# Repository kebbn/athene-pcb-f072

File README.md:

# athene-pcb-f072
 65% PCB design for the Athene keyboard by KL using the STM32F072 MCU.

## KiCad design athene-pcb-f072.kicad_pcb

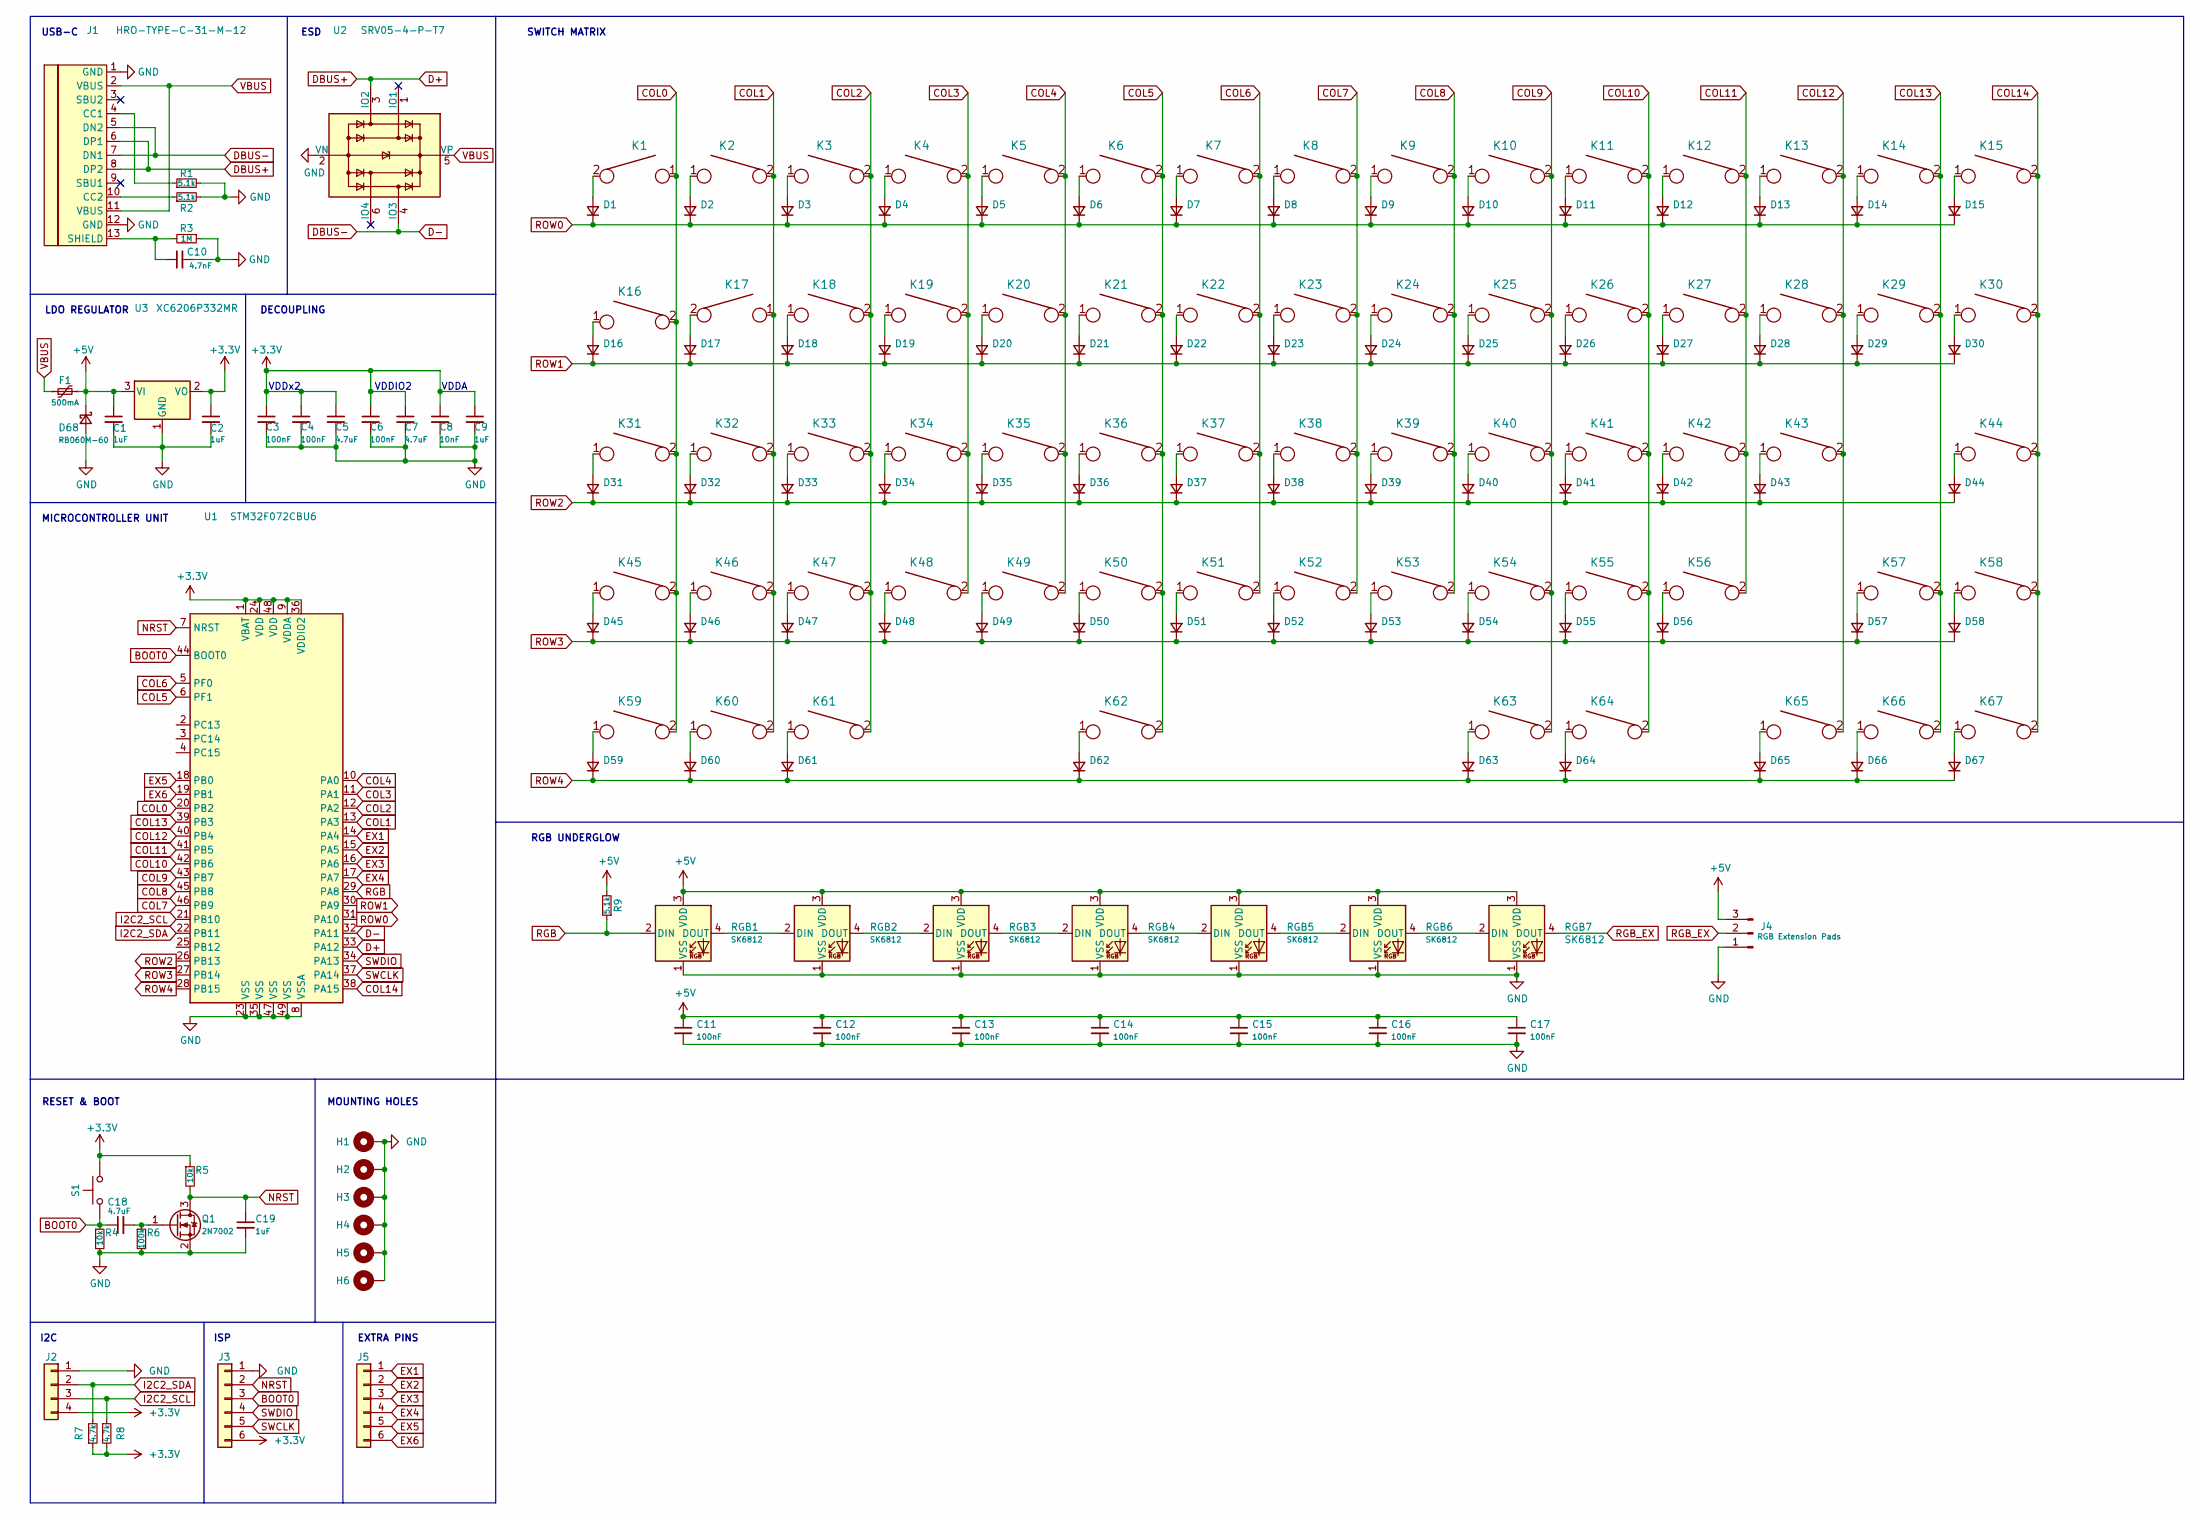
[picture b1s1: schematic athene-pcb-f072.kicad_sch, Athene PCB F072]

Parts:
C1, C2, C9: 1uF; C_0805_2012Metric; LCSC C28323
C3, C4, C6, C11, C12, C13, C14, C15, C16, C17: 100nF; C_0805_2012Metric; LCSC C49678
C5, C7: 4.7uF; C_0805_2012Metric; LCSC C1779
C8: 10nF; C_0805_2012Metric; LCSC C1710
C10: 4.7nF; C_0805_2012Metric; LCSC C1744
C18: 4.7uF; C_0805_2012Metric; LCSC C1744
C19: 1uF; C_0805_2012Metric; LCSC C15850
D1, D2, D3, D4, D5, D6, D7, D8, D9, D10, D11, D12, D13, D14, D15, D16, D17, D18, D19, D20, D21, D22, D23, D24, D25, D26, D27, D28, D29, D30, D31, D32, D33, D34, D35, D36, D37, D38, D39, D40, D41, D42, D43, D44, D45, D46, D47, D48, D49, D50, D51, D52, D53, D54, D55, D56, D57, D58, D59, D60, D61, D62, D63, D64, D65, D66, D67: 1N4148W; D_SOD-123; LCSC C81598
D68: RB060M-60; D_SOD-123; LCSC C115330
F1: 500mA; Fuse_1206_3216Metric; LCSC C151162
H1, H2, H4, H6: Poker_oval_hole
H3, H5: MountingHole_M2
J1: HRO-TYPE-C-31-M-12
J2: I2C; SolderWirePad_1x04_P3.175mm_Drill0.8mm
J3: ISP; ICSP-Header
J4: RGB Extension Pads; SolderWirePad_1x03_P3.175mm_Drill0.8mm
J5: EX; 6-Pin Header
K1, K2, K3, K4, K5, K6, K7, K8, K9, K10, K11, K12, K13, K14, K15, K16, K17, K18, K19, K20, K21, K22, K23, K24, K25, K26, K27, K28, K30, K31, K32, K33, K34, K35, K36, K38, K39, K40, K41, K42, K43, K44, K45, K46, K47, K48, K49, K50, K51, K52, K53, K54, K55, K56, K57, K58, K59, K61, K62, K63, K64, K65, K67: KEYSW; Kailh_MX_Socket (3D)
K29, K37, K60, K66: KEYSW; Kailh_MX_Socket (3D) 1_Circle
Q1: 2N7002; SOT-23; LCSC C8545
R1, R2, R9: 5.1k; R_0805_2012Metric; LCSC C27834
R3: 1M; R_0805_2012Metric; LCSC C17514
R4, R5: 10k; R_0805_2012Metric; LCSC C17414
R6: 100k; R_0805_2012Metric; LCSC C17407
R7, R8: 4.7k; R_0805_2012Metric; LCSC C17673
RGB1, RGB2, RGB3, RGB4, RGB5, RGB6, RGB7: SK6812; SK6812_Mini
S1: TS-1187A-B-A-B; SKQG-1155865; LCSC C318884
U1: STM32F072CBU6; QFN-48-1EP_7x7mm_P0.5mm_EP5.6x5.6mm; LCSC C92504
U2: SRV05-4-P-T7; SOT-23-6; LCSC C85364
U3: XC6206P332MR; SOT-23; LCSC C5446

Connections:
+3V3: C2.1, C3.1, C4.1, C5.1, C6.1, C7.1, C8.1, C9.1, J2.4, J3.6, R5.1, R7.1, R8.2, S1.2, U1.1 (VBAT), U1.9 (VDDA), U1.24 (VDD), U1.36 (VDDIO2), U1.48 (VDD), U3.2 (VO)
+5V: C1.1, C11.1, C12.1, C13.1, C14.1, C15.1, C16.1, C17.1, D68.1 (K), F1.2, J4.3, R9.2, RGB1.3 (VDD), RGB2.3 (VDD), RGB3.3 (VDD), RGB4.3 (VDD), RGB5.3 (VDD), RGB6.3 (VDD), RGB7.3 (VDD), U3.3 (VI)
BOOT0: C18.1, J3.3, R4.1, S1.1, U1.44 (BOOT0)
COL0: K1.1, K16.2, K31.2, K45.2, K59.2, U1.20 (PB2)
COL1: K2.2, K17.1, K32.2, K46.2, K60.2, U1.13 (PA3)
COL2: K3.2, K18.2, K33.2, K47.2, K61.2, U1.12 (PA2)
COL3: K4.2, K19.2, K34.2, K48.2, U1.11 (PA1)
COL4: K5.2, K20.2, K35.2, K49.2, U1.10 (PA0)
COL5: K6.2, K21.2, K36.2, K50.2, K62.2, U1.6 (PF1)
COL6: K7.2, K22.2, K37.2, K51.2, U1.5 (PF0)
COL7: K8.2, K23.2, K38.2, K52.2, U1.46 (PB9)
COL8: K9.2, K24.2, K39.2, K53.2, U1.45 (PB8)
COL9: K10.2, K25.2, K40.2, K54.2, K63.2, U1.43 (PB7)
COL10: K11.2, K26.2, K41.2, K55.2, K64.2, U1.42 (PB6)
COL11: K12.2, K27.2, K42.2, K56.2, U1.41 (PB5)
COL12: K13.2, K28.2, K43.2, K65.2, U1.40 (PB4)
COL13: K14.2, K29.2, K57.2, K66.2, U1.39 (PB3)
COL14: K15.2, K30.2, K44.2, K58.2, K67.2, U1.38 (PA15)
D+: J1.6 (DP1), J1.8 (DP2), U1.33 (PA12), U2.3 (IO2)
D-: J1.5 (DN2), J1.7 (DN1), U1.32 (PA11), U2.4 (IO3)
EX1: J5.1, U1.14 (PA4)
EX2: J5.2, U1.15 (PA5)
EX3: J5.3, U1.16 (PA6)
EX4: J5.4, U1.17 (PA7)
EX5: J5.5, U1.18 (PB0)
EX6: J5.6, U1.19 (PB1)
GND: C1.2, C2.2, C3.2, C4.2, C5.2, C6.2, C7.2, C8.2, C9.2, C10.2, C11.2, C12.2, C13.2, C14.2, C15.2, C16.2, C17.2, C19.2, D68.2 (A), H1.1, H2.1, H3.1, H4.1, H5.1, H6.1, J1.1 (GND), J1.12 (GND), J2.1, J3.1, J4.1, Q1.2 (S), R1.2, R2.2, R3.1, R4.2, R6.2, RGB1.1 (VSS), RGB2.1 (VSS), RGB3.1 (VSS), RGB4.1 (VSS), RGB5.1 (VSS), RGB6.1 (VSS), RGB7.1 (VSS), U1.8 (VSSA), U1.23 (VSS), U1.35 (VSS), U1.47 (VSS), U1.49 (VSS), U2.2 (VN), U3.1 (GND)
I2C2_SCL: J2.3, R8.1, U1.21 (PB10)
I2C2_SDA: J2.2, R7.2, U1.22 (PB11)
NRST: C19.1, J3.2, Q1.3 (D), R5.2, U1.7 (NRST)
unnamed: C10.1, J1.13 (SHIELD), R3.2
unnamed: C18.2, Q1.1 (G), R6.1
unnamed: D1.2 (A), K1.2
unnamed: D2.2 (A), K2.1
unnamed: D3.2 (A), K3.1
unnamed: D4.2 (A), K4.1
unnamed: D5.2 (A), K5.1
unnamed: D6.2 (A), K6.1
unnamed: D7.2 (A), K7.1
unnamed: D8.2 (A), K8.1
unnamed: D9.2 (A), K9.1
unnamed: D10.2 (A), K10.1
unnamed: D11.2 (A), K11.1
unnamed: D12.2 (A), K12.1
unnamed: D13.2 (A), K13.1
unnamed: D14.2 (A), K14.1
unnamed: D15.2 (A), K15.1
unnamed: D16.2 (A), K16.1
unnamed: D17.2 (A), K17.2
unnamed: D18.2 (A), K18.1
unnamed: D19.2 (A), K19.1
unnamed: D20.2 (A), K20.1
unnamed: D21.2 (A), K21.1
unnamed: D22.2 (A), K22.1
unnamed: D23.2 (A), K23.1
unnamed: D24.2 (A), K24.1
unnamed: D25.2 (A), K25.1
unnamed: D26.2 (A), K26.1
unnamed: D27.2 (A), K27.1
unnamed: D28.2 (A), K28.1
unnamed: D29.2 (A), K29.1
unnamed: D30.2 (A), K30.1
unnamed: D31.2 (A), K31.1
unnamed: D32.2 (A), K32.1
unnamed: D33.2 (A), K33.1
unnamed: D34.2 (A), K34.1
unnamed: D35.2 (A), K35.1
unnamed: D36.2 (A), K36.1
unnamed: D37.2 (A), K37.1
unnamed: D38.2 (A), K38.1
unnamed: D39.2 (A), K39.1
unnamed: D40.2 (A), K40.1
unnamed: D41.2 (A), K41.1
unnamed: D42.2 (A), K42.1
unnamed: D43.2 (A), K43.1
unnamed: D44.2 (A), K44.1
unnamed: D45.2 (A), K45.1
unnamed: D46.2 (A), K46.1
unnamed: D47.2 (A), K47.1
unnamed: D48.2 (A), K48.1
unnamed: D49.2 (A), K49.1
unnamed: D50.2 (A), K50.1
unnamed: D51.2 (A), K51.1
unnamed: D52.2 (A), K52.1
unnamed: D53.2 (A), K53.1
unnamed: D54.2 (A), K54.1
unnamed: D55.2 (A), K55.1
unnamed: D56.2 (A), K56.1
unnamed: D57.2 (A), K57.1
unnamed: D58.2 (A), K58.1
unnamed: D59.2 (A), K59.1
unnamed: D60.2 (A), K60.1
unnamed: D61.2 (A), K61.1
unnamed: D62.2 (A), K62.1
unnamed: D63.2 (A), K63.1
unnamed: D64.2 (A), K64.1
unnamed: D65.2 (A), K65.1
unnamed: D66.2 (A), K66.1
unnamed: D67.2 (A), K67.1
unnamed: J1.4 (CC1), R1.1
unnamed: J1.10 (CC2), R2.1
unnamed: RGB1.4 (DOUT), RGB2.2 (DIN)
unnamed: RGB2.4 (DOUT), RGB3.2 (DIN)
unnamed: RGB3.4 (DOUT), RGB4.2 (DIN)
unnamed: RGB4.4 (DOUT), RGB5.2 (DIN)
unnamed: RGB5.4 (DOUT), RGB6.2 (DIN)
unnamed: RGB6.4 (DOUT), RGB7.2 (DIN)
RGB: R9.1, RGB1.2 (DIN), U1.29 (PA8)
RGB_EX: J4.2, RGB7.4 (DOUT)
ROW0: D1.1 (K), D2.1 (K), D3.1 (K), D4.1 (K), D5.1 (K), D6.1 (K), D7.1 (K), D8.1 (K), D9.1 (K), D10.1 (K), D11.1 (K), D12.1 (K), D13.1 (K), D14.1 (K), D15.1 (K), U1.31 (PA10)
ROW1: D16.1 (K), D17.1 (K), D18.1 (K), D19.1 (K), D20.1 (K), D21.1 (K), D22.1 (K), D23.1 (K), D24.1 (K), D25.1 (K), D26.1 (K), D27.1 (K), D28.1 (K), D29.1 (K), D30.1 (K), U1.30 (PA9)
ROW2: D31.1 (K), D32.1 (K), D33.1 (K), D34.1 (K), D35.1 (K), D36.1 (K), D37.1 (K), D38.1 (K), D39.1 (K), D40.1 (K), D41.1 (K), D42.1 (K), D43.1 (K), D44.1 (K), U1.26 (PB13)
ROW3: D45.1 (K), D46.1 (K), D47.1 (K), D48.1 (K), D49.1 (K), D50.1 (K), D51.1 (K), D52.1 (K), D53.1 (K), D54.1 (K), D55.1 (K), D56.1 (K), D57.1 (K), D58.1 (K), U1.27 (PB14)
ROW4: D59.1 (K), D60.1 (K), D61.1 (K), D62.1 (K), D63.1 (K), D64.1 (K), D65.1 (K), D66.1 (K), D67.1 (K), U1.28 (PB15)
SWCLK: J3.5, U1.37 (PA14)
SWDIO: J3.4, U1.34 (PA13)
VBUS: F1.1, J1.2 (VBUS), J1.11 (VBUS), U2.5 (VP)

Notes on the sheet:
LDO REGULATOR
I2C
USB-C
RESET & BOOT
MICROCONTROLLER UNIT
ISP
DECOUPLING
VDDx2
ESD
VDDIO2
MOUNTING HOLES
EXTRA PINS
VDDA
SWITCH MATRIX
RGB UNDERGLOW

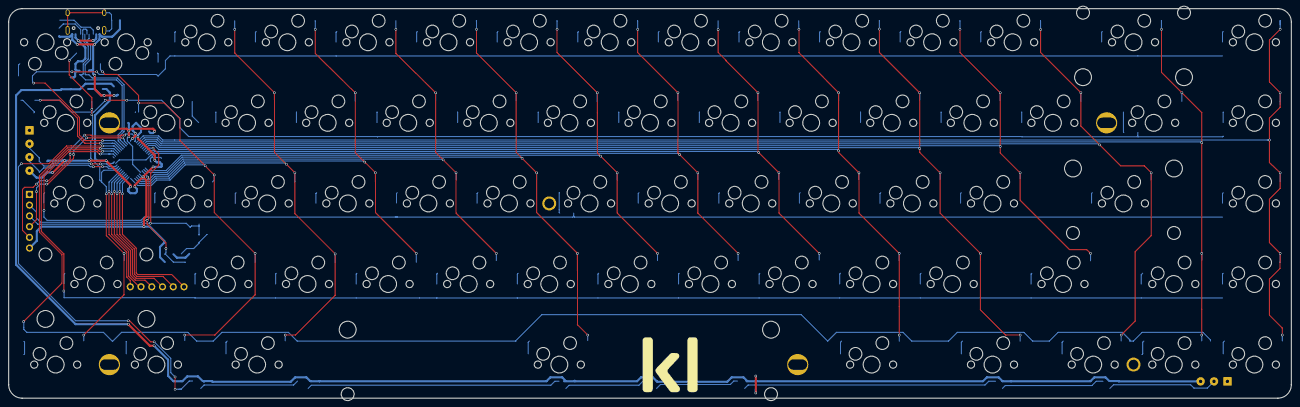
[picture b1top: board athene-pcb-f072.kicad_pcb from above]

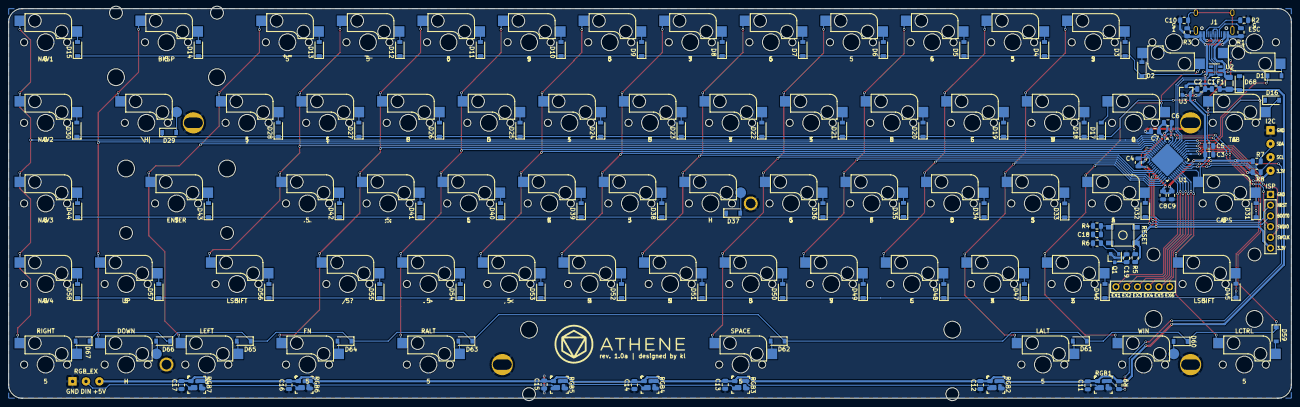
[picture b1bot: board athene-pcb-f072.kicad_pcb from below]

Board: 2 copper layers, 303.2 x 92.1 mm, 193 parts (181 on the bottom side), 117 nets.

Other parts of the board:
ST_BKSP: Stabilizer; Mx_Stab_200
ST_ENTER: Stabilizer; Mx_Stab_225
ST_LSHIFT: Stabilizer; Mx_Stab_200
ST_SPACE: Stabilizer; Mx_Stab_625
athene logo: LOGO; athene
kl logo: LOGO; kl

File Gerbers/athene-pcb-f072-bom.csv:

Comment,Designator,Footprint,LCSC
1uF,"C1,C2,C9,C19",Capacitor_SMD:C_0805_2012Metric,C28323
4.7nF,C10,Capacitor_SMD:C_0805_2012Metric,C1744
100nF,"C3,C4,C6,C11,C12,C13,C14,C15,C16,C17",Capacitor_SMD:C_0805_2012Metric,C49678
4.7uF,"C5,C7,C18",Capacitor_SMD:C_0805_2012Metric,C1779
10nF,C8,Capacitor_SMD:C_0805_2012Metric,C1710
1N4148W,"D1,D2,D3,D4,D5,D6,D7,D8,D9,D10,D11,D12,D13,D14,D15,D16,D17,D18,D19,D20,D21,D22,D23,D24,D25,D26,D27,D28,D29,D30,D31,D32,D33,D34,D35,D36,D37,D38,D39,D40,D41,D42,D43,D44,D45,D46,D47,D48,D49,D50,D51,D52,D53,D54,D55,D56,D57,D58,D59,D60,D61,D62,D63,D64,D65,D66,D67",Diode_SMD:D_SOD-123,C81598
RB060M-60,D68,Diode_SMD:D_SOD-123,C115330
500mA,F1,Fuse:Fuse_1206_3216Metric,C151162
2N7002,Q1,Package_TO_SOT_SMD:SOT-23,C8545
5.1k,"R1,R2,R9",Resistor_SMD:R_0805_2012Metric,C27834
1M,R3,Resistor_SMD:R_0805_2012Metric,C17514
10k,"R4,R5",Resistor_SMD:R_0805_2012Metric,C17414
100k,R6,Resistor_SMD:R_0805_2012Metric,C17407
4.7k,"R7,R8",Resistor_SMD:R_0805_2012Metric,C17673
TS-1187A-B-A-B,S1,random-keyboard-parts:SKQG-1155865,C318884
STM32F072CBU6,U1,Package_DFN_QFN:QFN-48-1EP_7x7mm_P0.5mm_EP5.6x5.6mm,C92504
SRV05-4-P-T7,U2,Package_TO_SOT_SMD:SOT-23-6,C85364
XC6206P332MR,U3,Package_TO_SOT_SMD:SOT-23,C5446

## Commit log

2020-08-28 Initial Commit
    Cloned from 32u4
2020-08-31 V1.0a
2020-09-10 v1.0a update
2024-03-12 File cleanup
